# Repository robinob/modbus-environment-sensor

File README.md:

# Keskkonnasensor — Modbus RTU

STM32G031F8P6-based environmental sensor with RS-485/Modbus RTU slave interface. Measures temperature, humidity, and air quality (eCO2/TVOC) via a snap-off remote sensor tab, reporting over an RS-485 daisy-chain bus to a Modbus RTU master.

## Key specs
- MCU: STM32G031F8P6 (TSSOP20)
- Sensors: SHT45 (temp/humidity), ENS160 (air quality), on a separate snap-off tab, panelized with the main board via mouse-bite
- Interface: RS-485, MAX13487 transceiver, AutoDirection
- Power: 12-30V DC input, MCP16301 buck → 5V, TLV70433 LDO → 3.3V (tab: MCP1700 → 1.8V for ENS160)
- 2-layer PCB, JLCPCB manufacturable

## Repo structure
- `*.kicad_*` (root) — KiCad project files
- `manufacturing/` — Gerbers, drill files, and BOM for ordering
- `docs/` — schematic design documentation and pinout reference

## Status
PCB layout complete, DRC clean (0 unconnected items), ready for fabrication. Tab board's SHT45/ENS160 to be hand-soldered via hot air + stencil.

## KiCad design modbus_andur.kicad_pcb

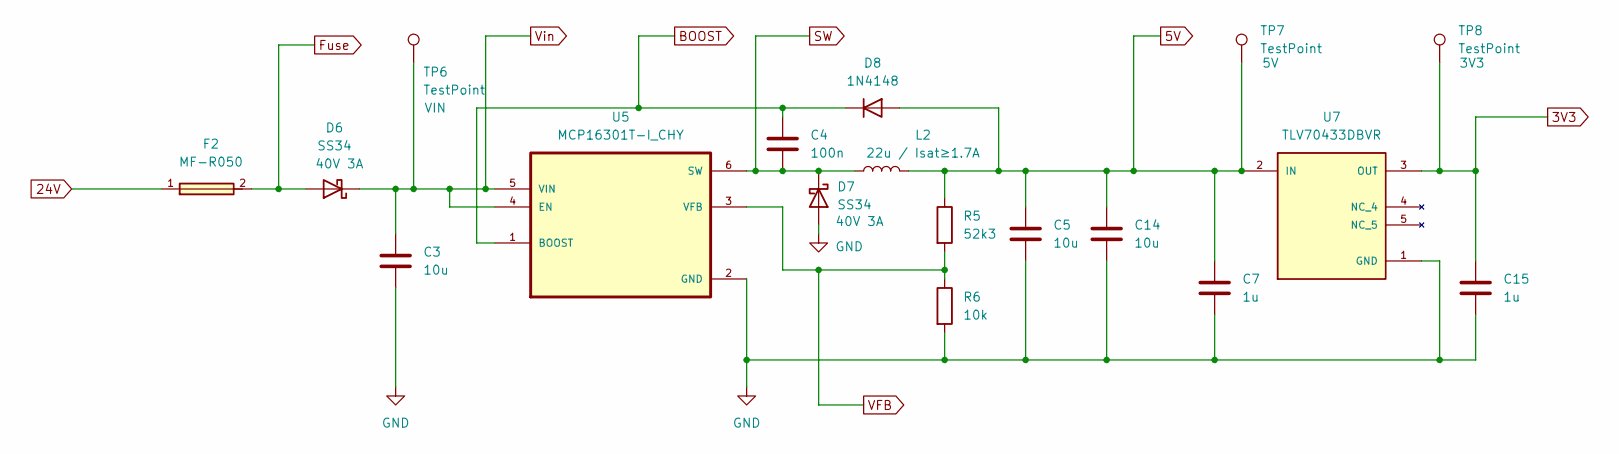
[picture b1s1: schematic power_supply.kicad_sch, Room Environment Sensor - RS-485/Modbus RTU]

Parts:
C3, C5, C14: 10u; C_0805_2012Metric_Pad1.18x1.45mm_HandSolder
C4: 100n; C_0805_2012Metric_Pad1.18x1.45mm_HandSolder
C7, C15: 1u; C_0805_2012Metric_Pad1.18x1.45mm_HandSolder
D6, D7: SS34; D_SMA
D8: 1N4148; D_DO-35_SOD27_P7.62mm_Horizontal
F2: MF-R050; FUSRB510W51L790T310H1370; MPN MF-R050
L2: 22u / Isat≥1.7A; IND_SLF7055T-220M1R7-3PF
R5: 52k3; R_0805_2012Metric_Pad1.20x1.40mm_HandSolder
R6: 10k; R_0805_2012Metric_Pad1.20x1.40mm_HandSolder
TP6, TP7, TP8: TestPoint; TestPoint_Keystone_5015_Micro_Mini
U5: MCP16301T-I_CHY; SOT95P270X145-6N
U7: TLV70433DBVR; SOT95P280X145-5N; PARTREV D

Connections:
3V3: C15.1, TP8.1, U7.3 (OUT); also elsewhere on the board
5V: C5.1, C7.1, C14.1, D8.2 (A), L2.2, R5.1, TP7.1, U7.2 (IN); also elsewhere on the board
24V: F2.1; also elsewhere on the board
BOOST: C4.1, D8.1 (K), U5.1 (BOOST)
Fuse: D6.2 (A), F2.2
GND: C3.2, C5.2, C7.2, C14.2, C15.2, D7.2 (A), R6.2, U5.2 (GND), U7.1 (GND); also elsewhere on the board
SW: C4.2, D7.1 (K), L2.1, U5.6 (SW)
VFB: R5.2, R6.1, U5.3 (VFB)
Vin: C3.1, D6.1 (K), TP6.1, U5.4 (EN), U5.5 (VIN)

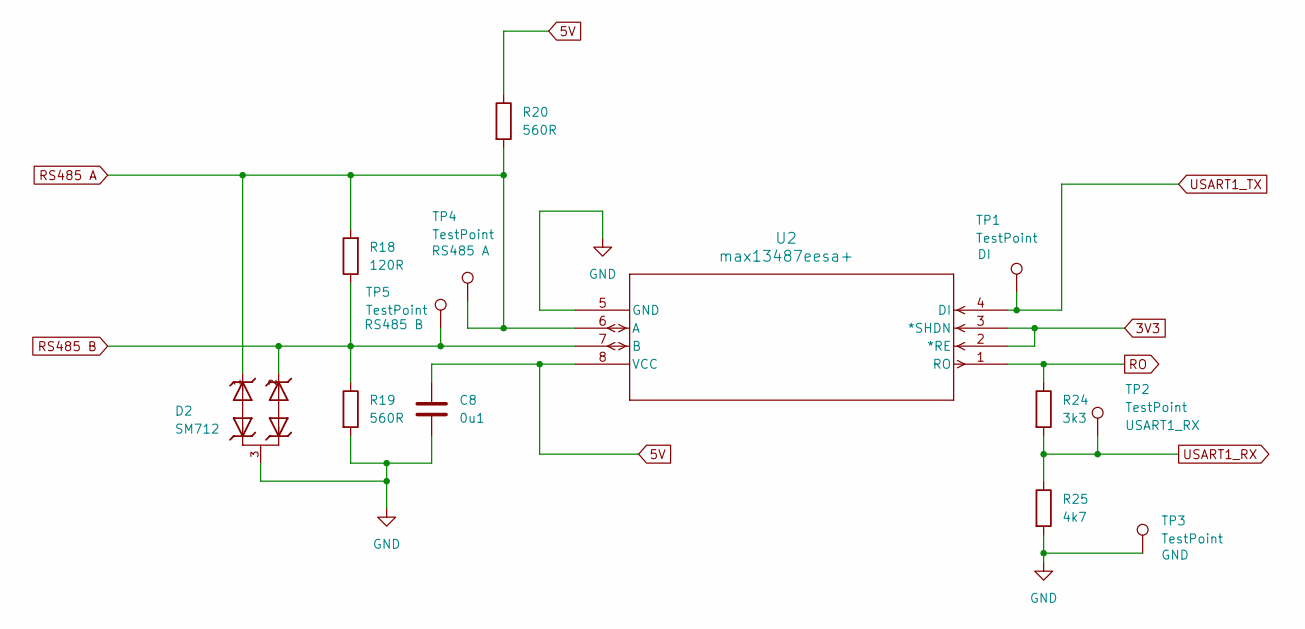
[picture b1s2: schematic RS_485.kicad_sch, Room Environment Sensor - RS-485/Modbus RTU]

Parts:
C8: 0u1; C_0805_2012Metric_Pad1.18x1.45mm_HandSolder
D2: SM712; SOT23; PART_MANUFACTURER Semtech
R18: 120R; R_0805_2012Metric_Pad1.20x1.40mm_HandSolder
R19, R20: 560R; R_0805_2012Metric_Pad1.20x1.40mm_HandSolder
R24: 3k3; R_0805_2012Metric_Pad1.20x1.40mm_HandSolder
R25: 4k7; R_0805_2012Metric_Pad1.20x1.40mm_HandSolder
TP1, TP2, TP3, TP4, TP5: TestPoint; TestPoint_Keystone_5015_Micro_Mini
U2: max13487eesa+; 21-0041B_8_MXM

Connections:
3V3: U2.2 (*RE), U2.3 (*SHDN); also elsewhere on the board
5V: C8.1, R20.1, U2.8 (VCC); also elsewhere on the board
GND: C8.2, D2.3, R19.2, R25.2, TP3.1, U2.5 (GND); also elsewhere on the board
RO: R24.1, U2.1 (RO)
RS485 A: D2.1, R18.2, R20.2, TP4.1, U2.6 (A); also elsewhere on the board
RS485 B: D2.2, R18.1, R19.1, TP5.1, U2.7 (B); also elsewhere on the board
USART1_RX: R24.2, R25.1, TP2.1; also elsewhere on the board
USART1_TX: TP1.1, U2.4 (DI); also elsewhere on the board

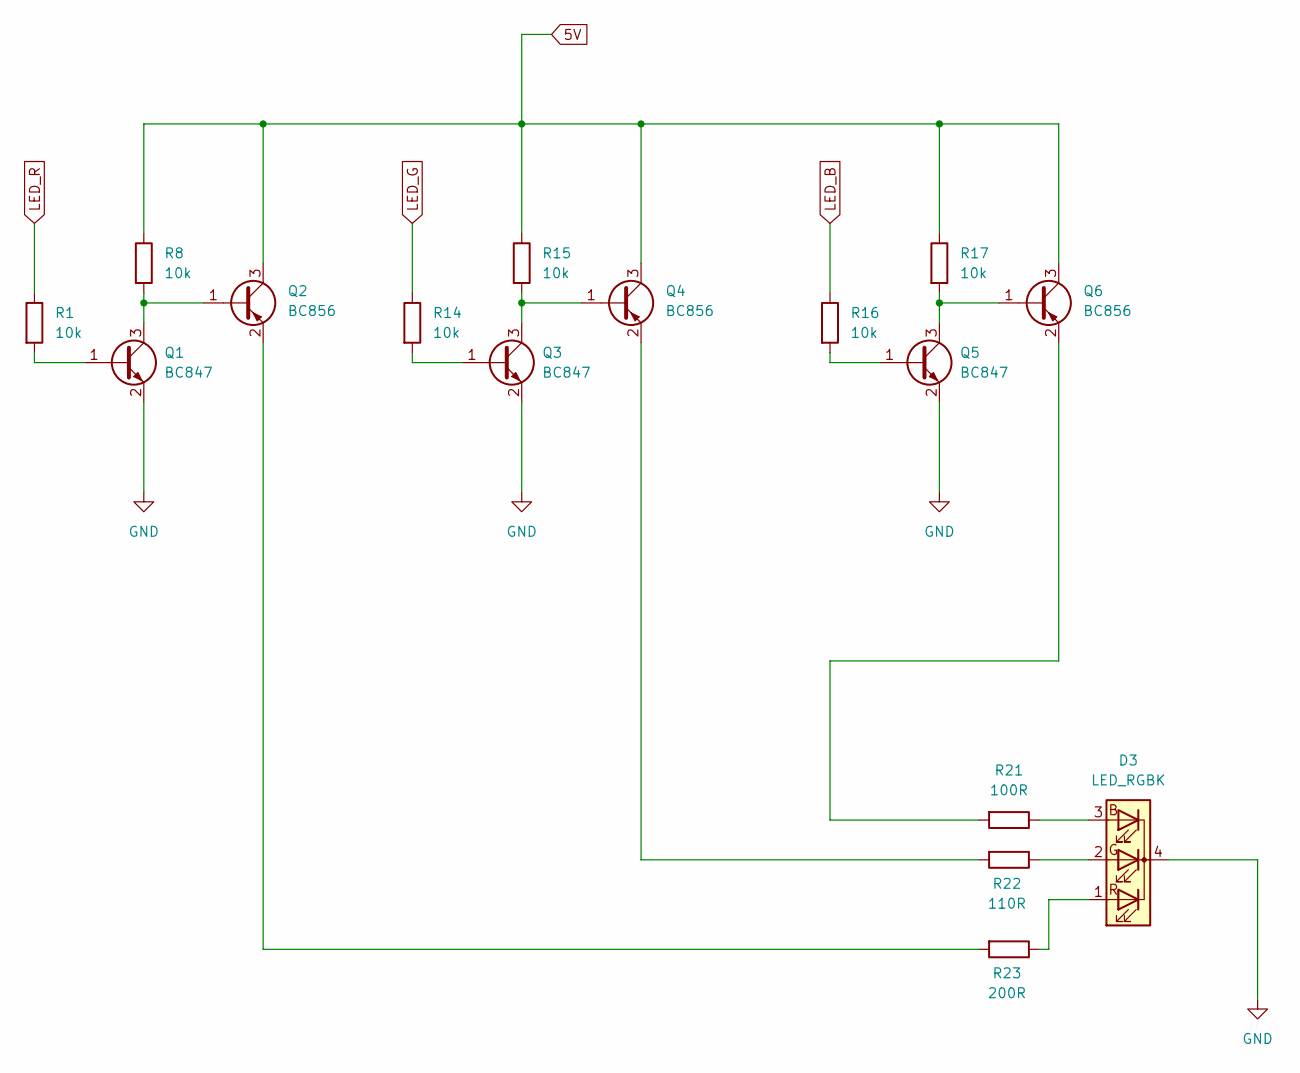
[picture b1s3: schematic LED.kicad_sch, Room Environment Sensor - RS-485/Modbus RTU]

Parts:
D3: LED_RGBK; LED_D5.0mm-4_RGB_Wide_Pins
Q1, Q3, Q5: BC847; SOT-23
Q2, Q4, Q6: BC856; SOT-23
R1, R8, R14, R15, R16, R17: 10k; R_0805_2012Metric_Pad1.20x1.40mm_HandSolder
R21: 100R; R_0805_2012Metric_Pad1.20x1.40mm_HandSolder
R22: 110R; R_0805_2012Metric_Pad1.20x1.40mm_HandSolder
R23: 200R; R_0805_2012Metric_Pad1.20x1.40mm_HandSolder

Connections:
5V: Q2.3 (C), Q4.3 (C), Q6.3 (C), R8.1, R15.1, R17.1; also elsewhere on the board
GND: D3.4 (K), Q1.2 (E), Q3.2 (E), Q5.2 (E); also elsewhere on the board
LED_B: R16.1; also elsewhere on the board
LED_G: R14.1; also elsewhere on the board
LED_R: R1.1; also elsewhere on the board
unnamed: D3.3 (BA), R21.1
unnamed: D3.2 (GA), R22.1
unnamed: D3.1 (RA), R23.1
unnamed: Q1.1 (B), R1.2
unnamed: Q1.3 (C), Q2.1 (B), R8.2
unnamed: Q2.2 (E), R23.2
unnamed: Q3.1 (B), R14.2
unnamed: Q3.3 (C), Q4.1 (B), R15.2
unnamed: Q4.2 (E), R22.2
unnamed: Q5.1 (B), R16.2
unnamed: Q5.3 (C), Q6.1 (B), R17.2
unnamed: Q6.2 (E), R21.2

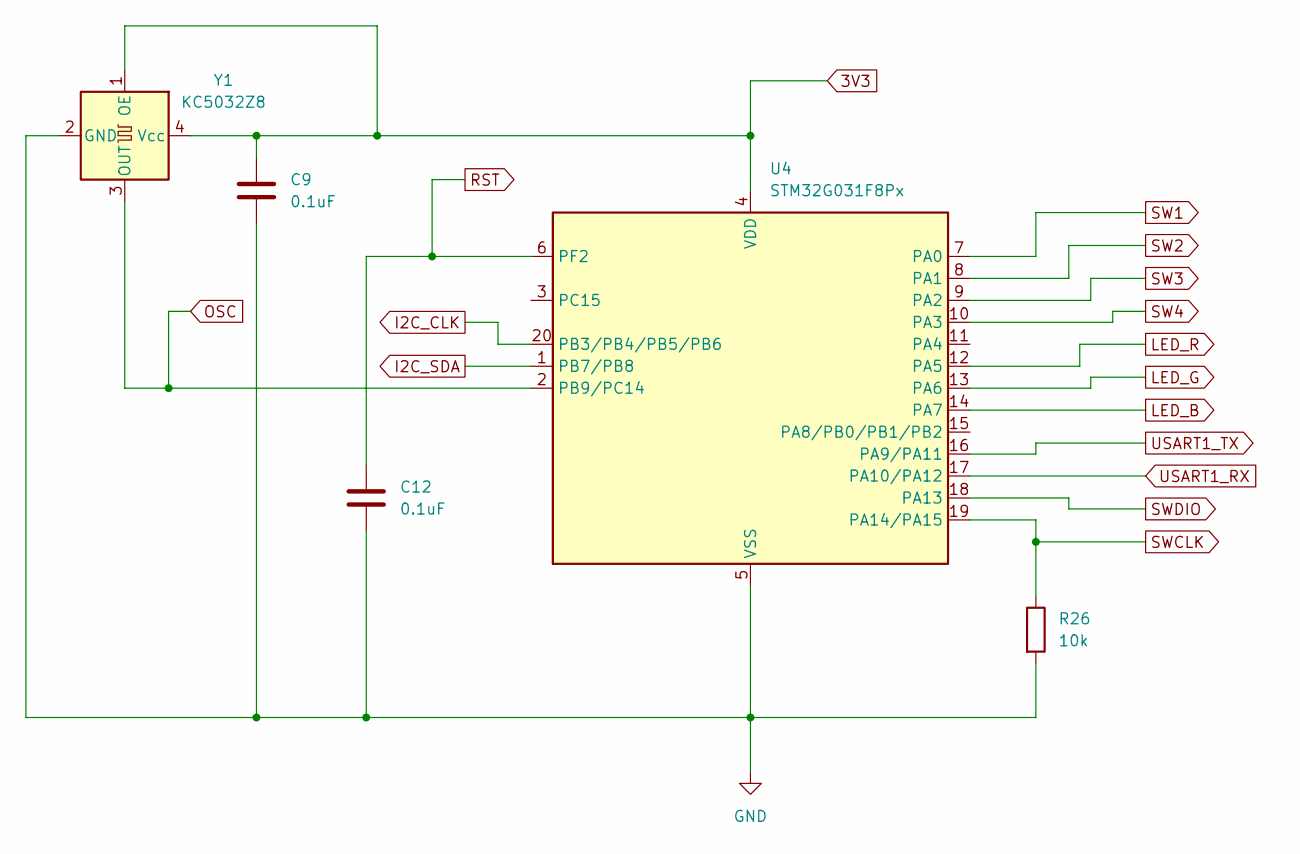
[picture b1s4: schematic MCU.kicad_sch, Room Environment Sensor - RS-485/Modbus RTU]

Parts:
C9, C12: 0.1uF; C_0805_2012Metric_Pad1.18x1.45mm_HandSolder
R26: 10k; R_0805_2012Metric_Pad1.20x1.40mm_HandSolder
U4: STM32G031F8Px; TSSOP-20_4.4x6.5mm_P0.65mm
Y1: KC5032Z8; Oscillator_SMD_SeikoEpson_SG8002LB-4Pin_5.0x3.2mm_HandSolde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

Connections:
3V3: C9.1, U4.4 (VDD), Y1.1 (OE), Y1.4 (Vcc); also elsewhere on the board
GND: C9.2, C12.2, R26.2, U4.5 (VSS), Y1.2 (GND); also elsewhere on the board
I2C_CLK: U4.20 (PB3/PB4/PB5/PB6); also elsewhere on the board
I2C_SDA: U4.1 (PB7/PB8); also elsewhere on the board
LED_B: U4.14 (PA7); also elsewhere on the board
LED_G: U4.13 (PA6); also elsewhere on the board
LED_R: U4.12 (PA5); also elsewhere on the board
OSC: U4.2 (PB9/PC14), Y1.3 (OUT)
RST: C12.1, U4.6 (PF2)
SW1: U4.7 (PA0); also elsewhere on the board
SW2: U4.8 (PA1); also elsewhere on the board
SW3: U4.9 (PA2); also elsewhere on the board
SW4: U4.10 (PA3); also elsewhere on the board
SWCLK: R26.1, U4.19 (PA14/PA15); also elsewhere on the board
SWDIO: U4.18 (PA13); also elsewhere on the board
USART1_RX: U4.17 (PA10/PA12); also elsewhere on the board
USART1_TX: U4.16 (PA9/PA11); also elsewhere on the board

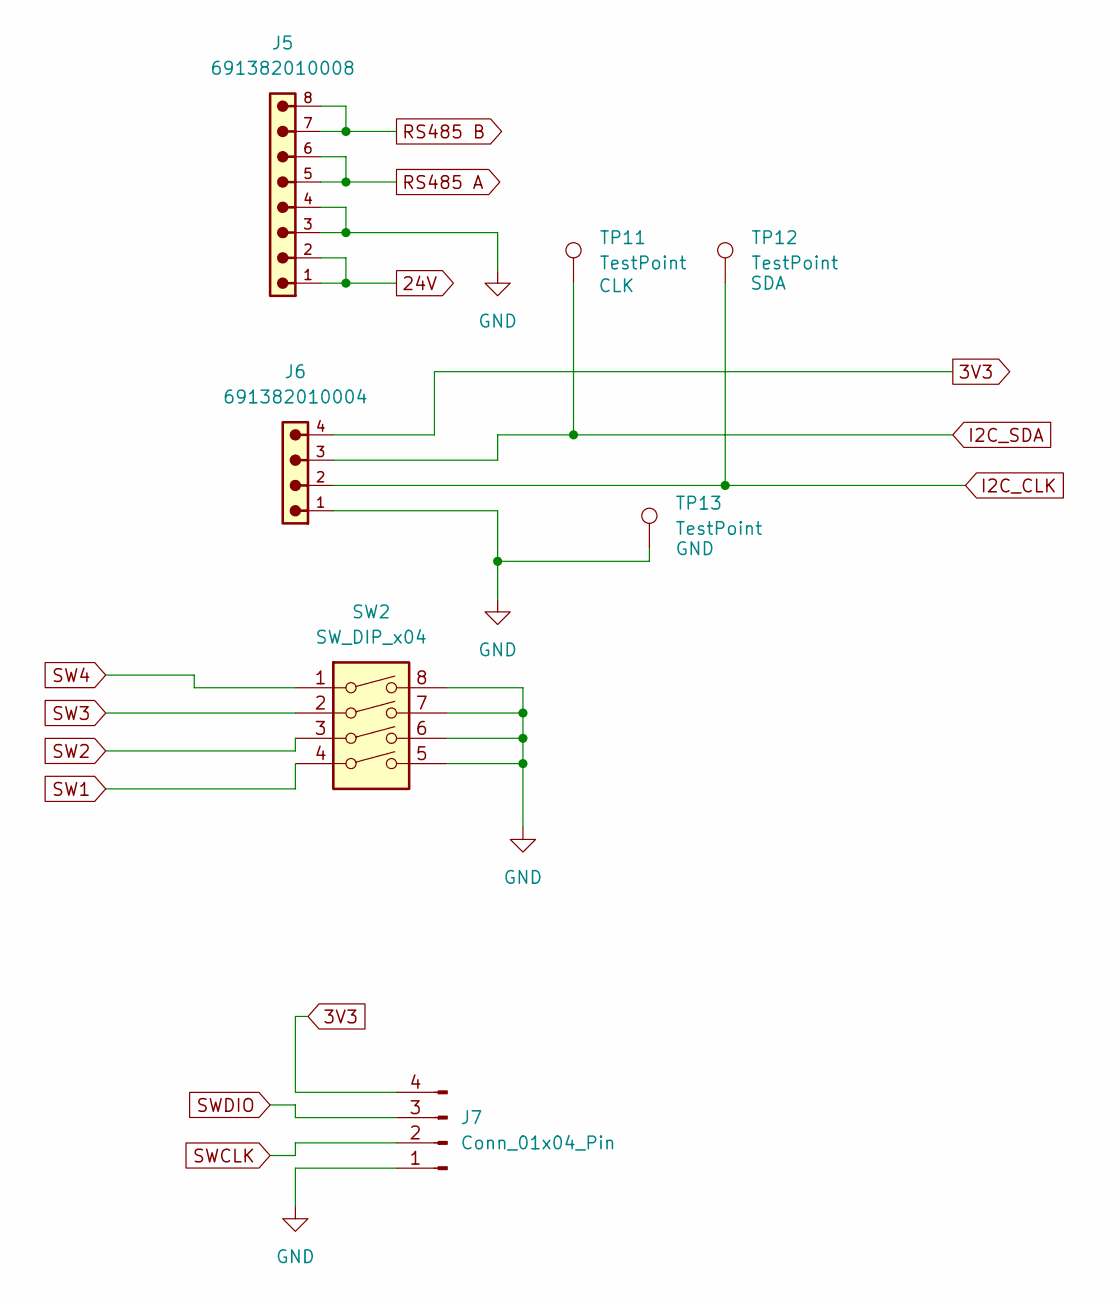
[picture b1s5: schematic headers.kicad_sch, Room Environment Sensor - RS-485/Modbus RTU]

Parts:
J5: 691382010008
J6: 691382010004
J7: Conn_01x04_Pin; PinHeader_1x04_P2.54mm_Vertical
SW2: SW_DIP_x04; SW_DIP_SPSTx04_Slide_9.78x12.34mm_W7.62mm_P2.54mm
TP11, TP12, TP13: TestPoint; TestPoint_Keystone_5015_Micro_Mini

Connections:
3V3: J6.4, J7.4; also elsewhere on the board
24V: J5.1, J5.2; also elsewhere on the board
GND: J5.3, J5.4, J6.1, J7.1, SW2.5, SW2.6, SW2.7, SW2.8, TP13.1; also elsewhere on the board
I2C_CLK: J6.2, TP12.1; also elsewhere on the board
I2C_SDA: J6.3, TP11.1; also elsewhere on the board
RS485 A: J5.5, J5.6; also elsewhere on the board
RS485 B: J5.7, J5.8; also elsewhere on the board
SW1: SW2.4; also elsewhere on the board
SW2: SW2.3; also elsewhere on the board
SW3: SW2.2; also elsewhere on the board
SW4: SW2.1; also elsewhere on the board
SWCLK: J7.2; also elsewhere on the board
SWDIO: J7.3; also elsewhere on the board

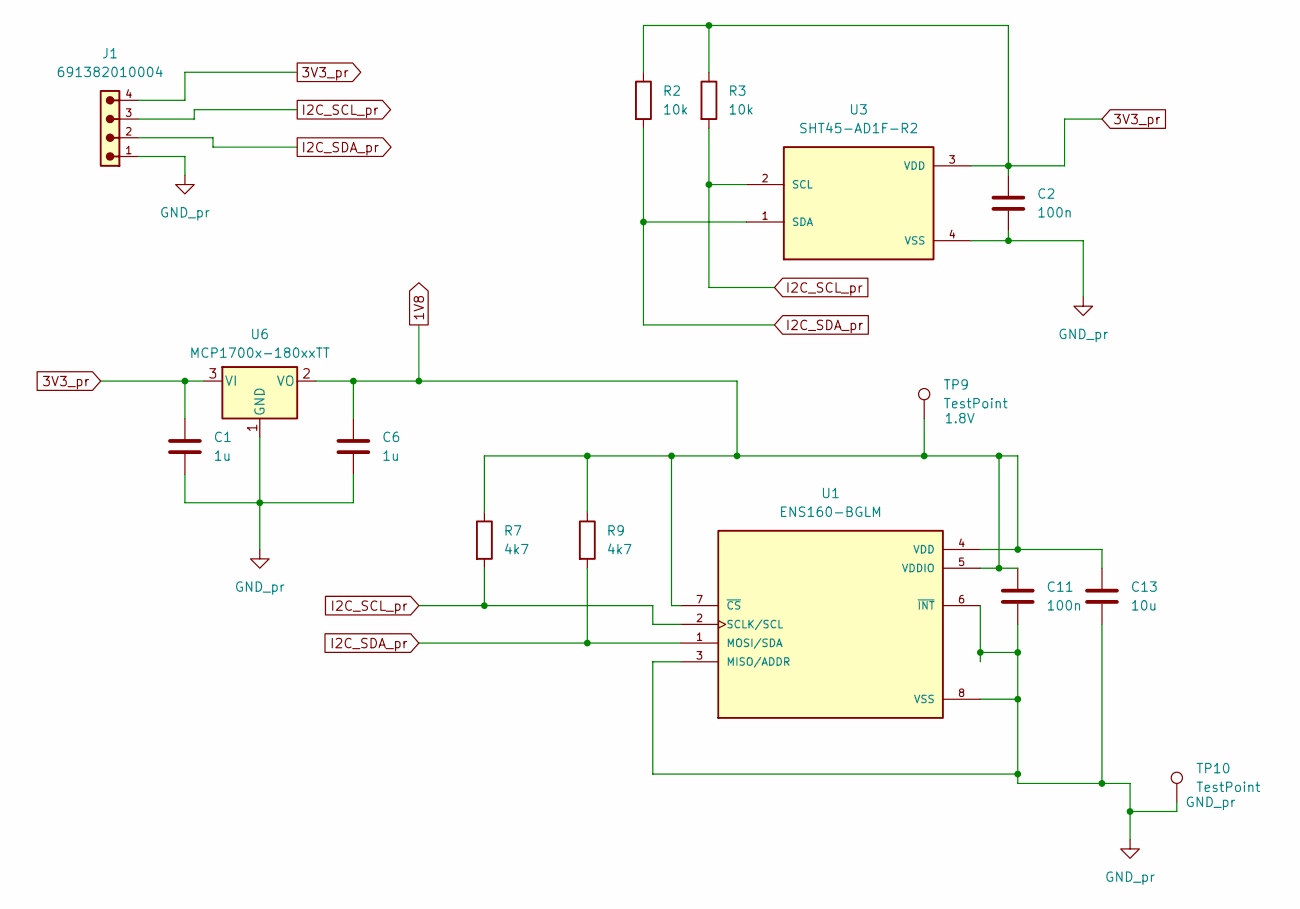
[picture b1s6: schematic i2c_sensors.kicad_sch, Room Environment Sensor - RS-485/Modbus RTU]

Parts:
C1, C6: 1u; C_0805_2012Metric_Pad1.18x1.45mm_HandSolder
C2, C11: 100n; C_0805_2012Metric_Pad1.18x1.45mm_HandSolder
C13: 10u; C_0805_2012Metric_Pad1.18x1.45mm_HandSolder
J1: 691382010004
R2, R3: 10k; R_0805_2012Metric_Pad1.20x1.40mm_HandSolder
R7, R9: 4k7; R_0805_2012Metric_Pad1.20x1.40mm_HandSolder
TP9, TP10: TestPoint; TestPoint_Keystone_5015_Micro_Mini
U1: ENS160-BGLM; XDCR_ENS160-BGLM; PARTREV 1.3
U3: SHT45-AD1F-R2; SHT4X
U6: MCP1700x-180xxTT; SOT-23

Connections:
1V8: C6.1, C11.1, C13.1, R7.1, R9.1, TP9.1, U1.4 (VDD), U1.5 (VDDIO), U1.7 (~CS), U6.2 (VO)
3V3_pr: C1.1, C2.1, J1.4, R2.1, R3.1, U3.3 (VDD), U6.3 (VI)
GND_pr: C1.2, C2.2, C6.2, C11.2, C13.2, J1.1, TP10.1, U1.3 (MISO/ADDR), U1.6 (~INT), U1.8 (VSS), U1.9 (VSS), U3.4 (VSS), U6.1 (GND)
I2C_SCL_pr: J1.3, R3.2, R7.2, U1.2 (SCLK/SCL), U3.2 (SCL)
I2C_SDA_pr: J1.2, R2.2, R9.2, U1.1 (MOSI/SDA), U3.1 (SDA)

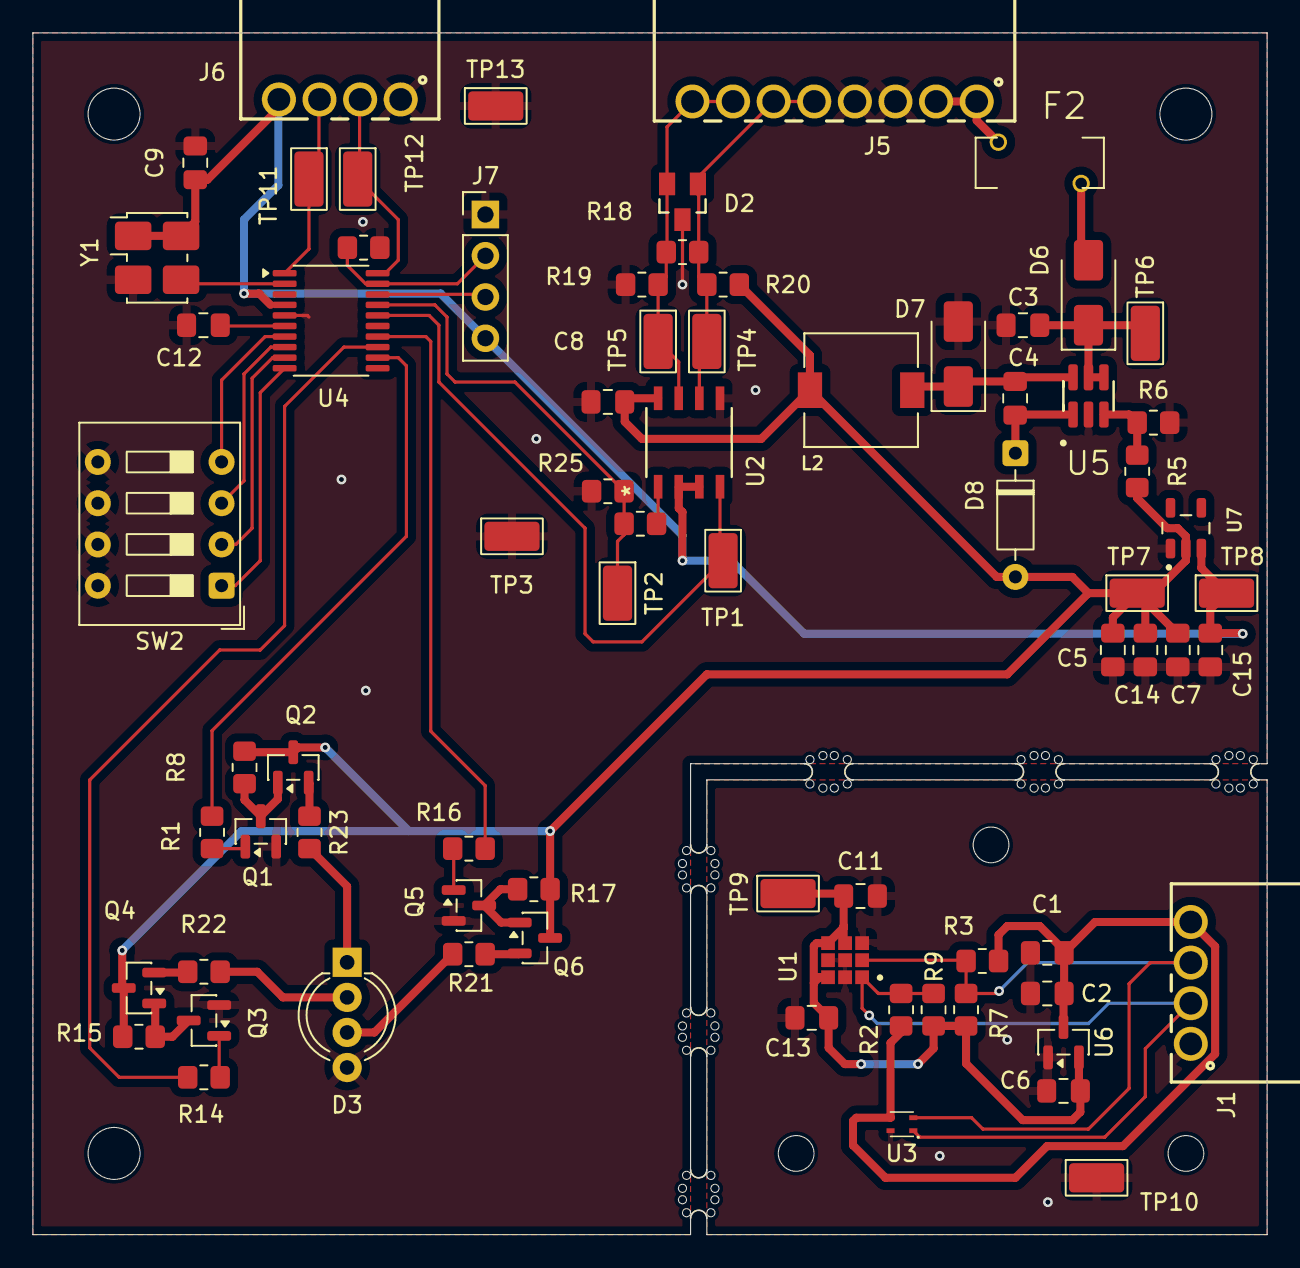
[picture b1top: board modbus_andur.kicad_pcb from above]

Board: 2 copper layers, 76.0 x 74.0 mm, 80 parts (0 on the bottom side), 44 nets.

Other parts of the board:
mouse-bite-1mm-slot, mouse-bite-1mm-slot#2, mouse-bite-1mm-slot#3, mouse-bite-1mm-slot#4, mouse-bite-1mm-slot#5, mouse-bite-1mm-slot#6: VAL**; mouse-bite-1mm-slot

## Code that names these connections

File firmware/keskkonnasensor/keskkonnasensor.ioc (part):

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Mcu.Name=STM32G031F(4-6-8)Px
Mcu.Package=TSSOP20
Mcu.UserName=STM32G031F8Px
PA0.GPIOParameters=GPIO_PuPd,GPIO_Label
PA0.GPIO_Label=DIP_1
PA0.GPIO_PuPd=GPIO_PULLUP
PA0.Signal=GPIO_Input
PA1.GPIOParameters=GPIO_PuPd,GPIO_Label
PA1.GPIO_Label=DIP_2
PA1.GPIO_PuPd=GPIO_PULLUP
PA1.Signal=GPIO_Input
PA10\ [PA12].Mode=Asynchronous
PA10\ [PA12].Signal=USART1_RX
PA13.Mode=Serial_Wire
PA13.Signal=SYS_SWDIO
PA14-BOOT0.Mode=Serial_Wire
PA14-BOOT0.Signal=SYS_SWCLK
PA14-BOOT0__PA15.StandardMode=true
PA2.GPIOParameters=GPIO_PuPd,GPIO_Label
PA2.GPIO_Label=DIP_3
PA2.GPIO_PuPd=GPIO_PULLUP
PA2.Signal=GPIO_Input
PA3.GPIOParameters=GPIO_PuPd,GPIO_Label
PA3.GPIO_Label=DIP_4
PA3.GPIO_PuPd=GPIO_PULLUP
PA3.Signal=GPIO_Input
PA5.GPIOParameters=GPIO_Label
PA5.GPIO_Label=LED_R
PA5.Signal=GPIO_Output
PA6.GPIOParameters=GPIO_Label
PA6.GPIO_Label=LED_G
PA6.Signal=GPIO_Output
PA7.GPIOParameters=GPIO_Label
PA7.GPIO_Label=LED_B
PA7.Signal=GPIO_Output
PA9\ [PA11].Mode=Asynchronous
PA9\ [PA11].Signal=USART1_TX
PB0__PB1__PB2__PA8.StandardMode=true
PB3__PB4__PB5__PB6.StandardMode=true
PB6.Mode=I2C
PB6.Signal=I2C1_SCL
PB7.Mode=I2C
PB7.Signal=I2C1_SDA
PB7__PB8.StandardMode=true
PC14-OSC32_IN\ (PC14).Mode=HSE-External-Clock-Source
PC14-OSC32_IN\ (PC14).Signal=RCC_OSC_IN
PC14-OSC32_IN\ (PC14)__PB9.StandardMode=true
RCC.HSE_VALUE=8000000
RCC.SYSCLKFreq_VALUE=64000000
RCC.SYSCLKSource=RCC_SYSCLKSOURCE_PLLCLK
board=custom
